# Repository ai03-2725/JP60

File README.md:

# JP60  
GH60互換疑似JISキーボードPCB  
GH60-compatible JIS-like hotswap keyboard PCB

Features  
- MITライセンスのもとでソース公開 / Open-source under the MIT license  
- Kailh製ソケットで全キーホットスワップ可能、はんだ付け無しで組み立て可能 / Fully hotswap  
- GH60対応の60％ケースで使用可能 / Compatible with GH60 standard cases  
- 一般的なキーサイズのみの日本語入力配列なので、GMKやePBTなどの標準キーキャップセットを使用可能 / Features a JIS-like key layout using standard keycap sizes   

[配列データ / Layout data](http://www.keyboard-layout-editor.com/#/gists/8acf5e6dbc672aa6a96d8ddba1245e7f)

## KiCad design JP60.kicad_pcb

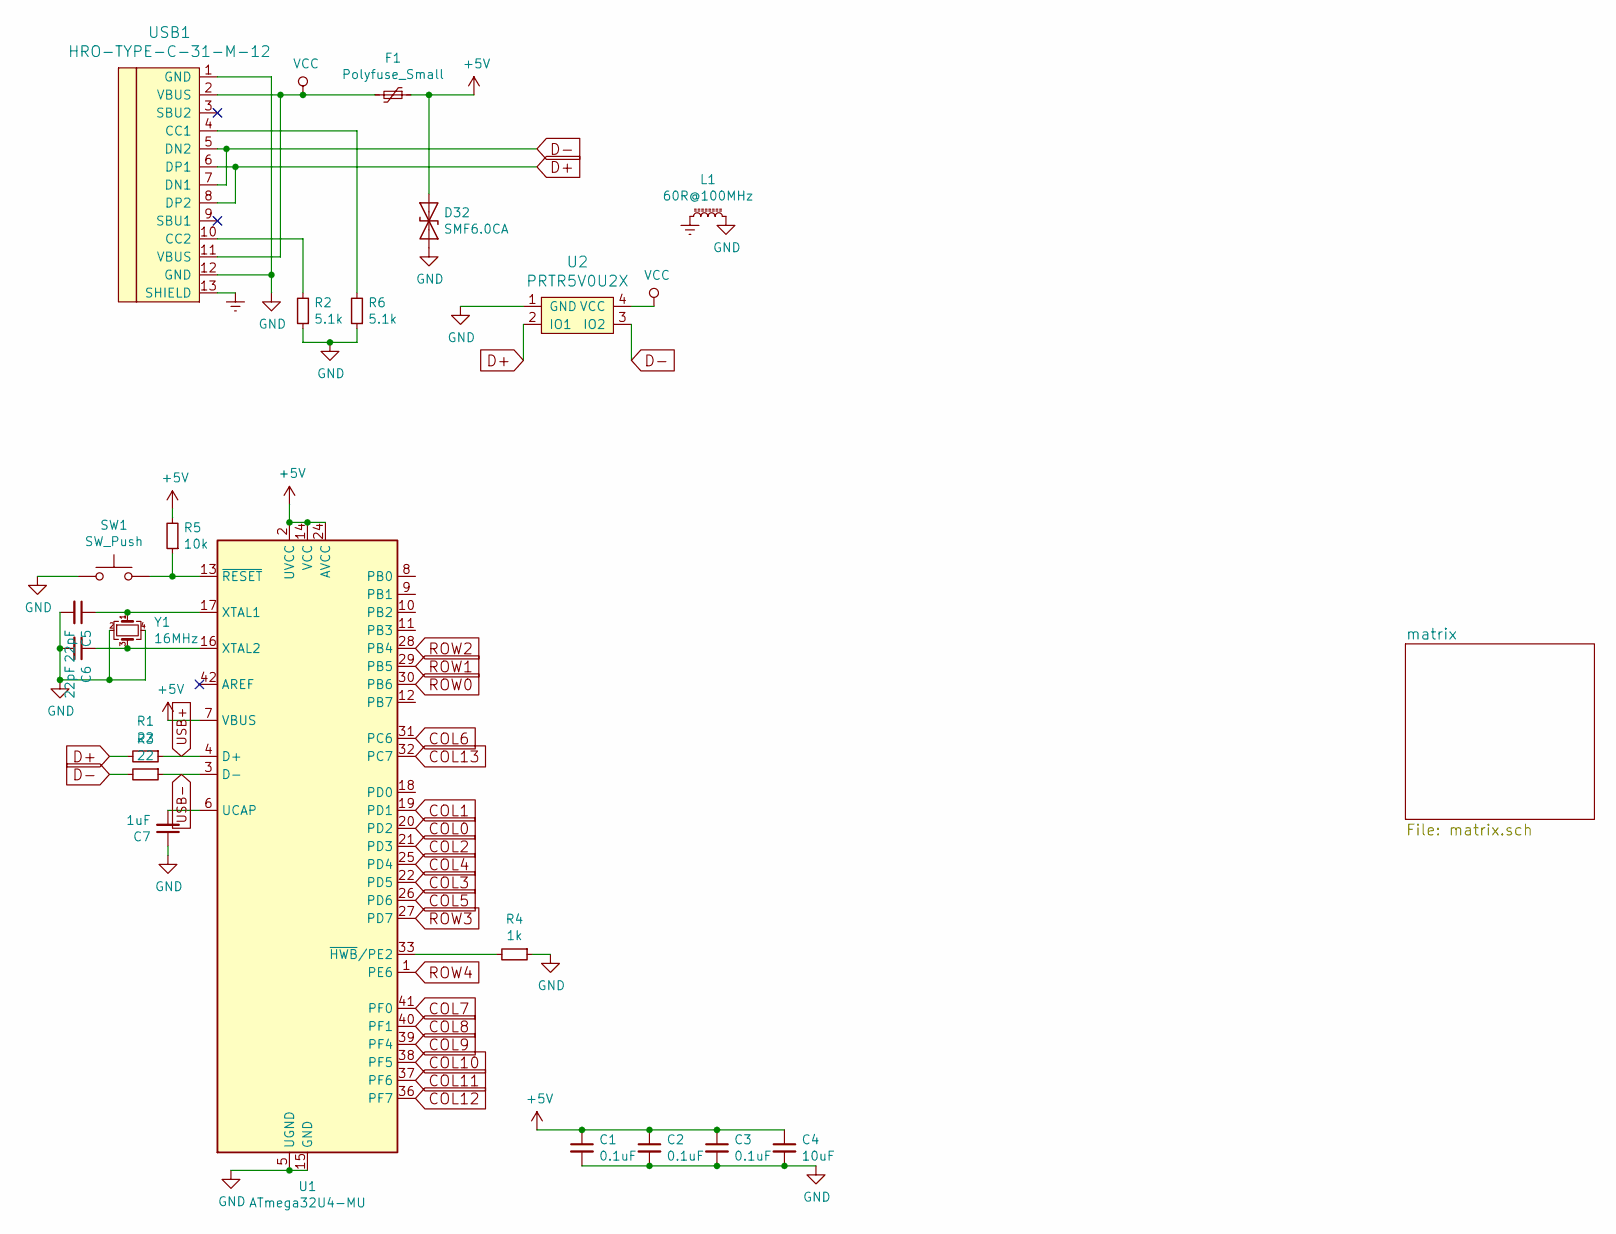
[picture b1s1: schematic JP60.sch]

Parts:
C1, C2, C3: 0.1uF; C_0603_1608Metric
C4: 10uF; C_0603_1608Metric
C5, C6: 22pF; C_0603_1608Metric
C7: 1uF; C_0603_1608Metric
D32: SMF6.0CA; D_SOD-123
F1: Polyfuse_Small; Fuse_1206_3216Metric
L1: 60R@100MHz; L_1206_3216Metric
R1, R3: 22; R_0603_1608Metric
R2, R6: 5.1k; R_0603_1608Metric
R4: 1k; R_0603_1608Metric
R5: 10k; R_0603_1608Metric
SW1: SW_Push; SW_SPST_TL3342
U1: ATmega32U4-MU; QFN-44-1EP_7x7mm_P0.5mm_EP5.2x5.2mm
U2: PRTR5V0U2X; SOT143B
USB1: HRO-TYPE-C-31-M-12; HRO-TYPE-C-31-M-12-Assembly
Y1: 16MHz; Crystal_SMD_3225-4Pin_3.2x2.5mm

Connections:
+5V: C1.1, C2.1, C3.1, C4.1, D32.2 (A2), F1.1, R5.2, U1.2 (UVCC), U1.7 (VBUS), U1.14 (VCC), U1.24 (AVCC), U1.34 (VCC), U1.44 (AVCC)
COL0: U1.20 (PD2); also elsewhere on the board
COL1: U1.19 (PD1); also elsewhere on the board
COL2: U1.21 (PD3); also elsewhere on the board
COL3: U1.22 (PD5); also elsewhere on the board
COL4: U1.25 (PD4); also elsewhere on the board
COL5: U1.26 (PD6); also elsewhere on the board
COL6: U1.31 (PC6); also elsewhere on the board
COL7: U1.41 (PF0); also elsewhere on the board
COL8: U1.40 (PF1); also elsewhere on the board
COL9: U1.39 (PF4); also elsewhere on the board
COL10: U1.38 (PF5); also elsewhere on the board
COL11: U1.37 (PF6); also elsewhere on the board
COL12: U1.36 (PF7); also elsewhere on the board
COL13: U1.32 (PC7); also elsewhere on the board
D+: R1.2, U2.2 (IO1), USB1.6 (DP1), USB1.8 (DP2)
D-: R3.2, U2.3 (IO2), USB1.5 (DN2), USB1.7 (DN1)
Earth: L1.1, USB1.13 (SHIELD)
GND: C1.2, C2.2, C3.2, C4.2, C5.2, C6.2, C7.1, D32.1 (A1), L1.2, R2.1, R4.1, R6.1, SW1.1, U1.5 (UGND), U1.15 (GND), U1.23 (GND), U1.35 (GND), U1.43 (GND), U1.45 (GND), U2.1 (GND), USB1.1 (GND), USB1.12 (GND), Y1.2, Y1.4
unnamed: C5.1, U1.17 (XTAL1), Y1.1
unnamed: C6.1, U1.16 (XTAL2), Y1.3
unnamed: C7.2, U1.6 (UCAP)
unnamed: R2.2, USB1.10 (CC2)
unnamed: R4.2, U1.33 (~HWB~/PE2)
unnamed: R5.1, SW1.2, U1.13 (~RESET)
unnamed: R6.2, USB1.4 (CC1)
ROW0: U1.30 (PB6); also elsewhere on the board
ROW1: U1.29 (PB5); also elsewhere on the board
ROW2: U1.28 (PB4); also elsewhere on the board
ROW3: U1.27 (PD7); also elsewhere on the board
ROW4: U1.1 (PE6); also elsewhere on the board
USB+: R1.1, U1.4 (D+)
USB-: R3.1, U1.3 (D-)
VCC: F1.2, U2.4 (VCC), USB1.2 (VBUS), USB1.11 (VBUS)

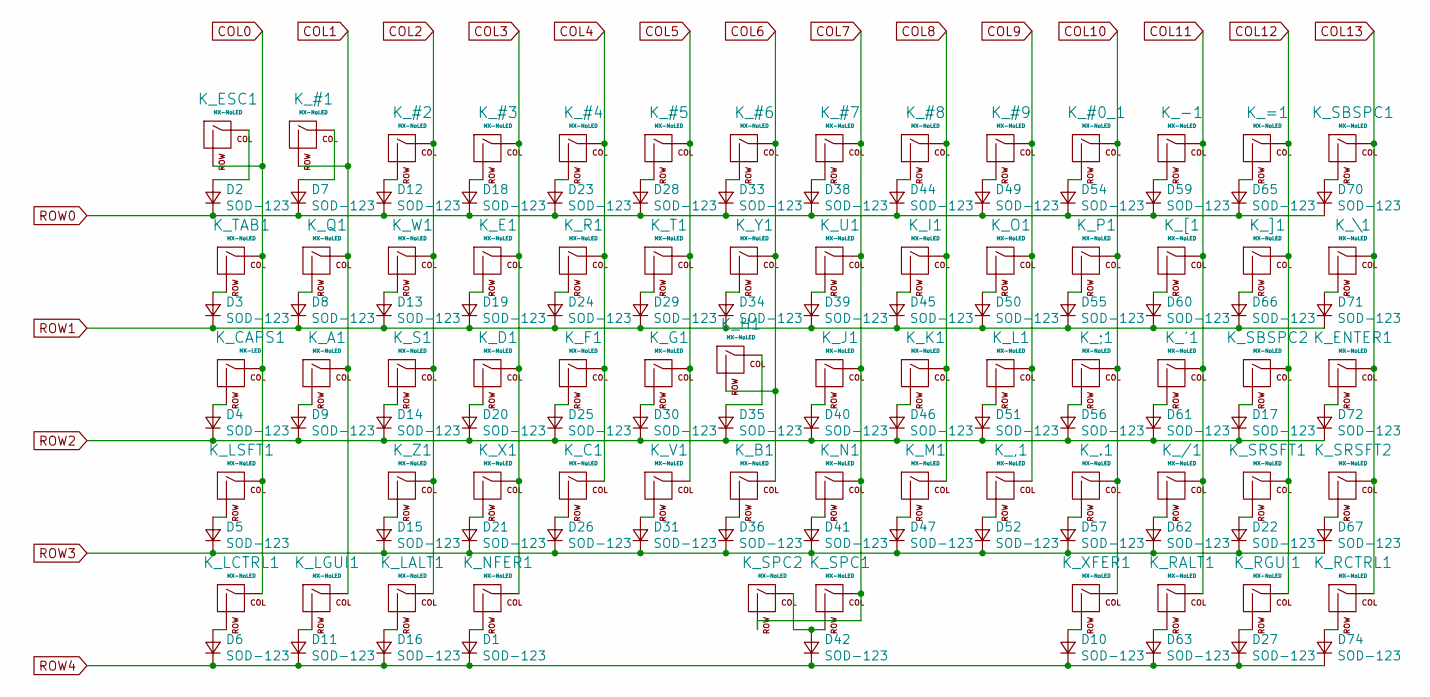
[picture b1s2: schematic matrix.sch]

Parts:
D1, D2, D3, D4, D5, D6, D7, D8, D9, D10, D11, D12, D13, D14, D15, D16, D17, D18, D19, D20, D21, D22, D23, D24, D25, D26, D27, D28, D29, D30, D31, D33, D34, D35, D36, D38, D39, D40, D41, D42, D44, D45, D46, D47, D49, D50, D51, D52, D54, D55, D56, D57, D59, D60, D61, D62, D63, D65, D66, D67, D70, D71, D72, D74: SOD-123; D_SOD-123
K_#0_1, K_#1, K_#2, K_#3, K_#4, K_#5, K_#6, K_#7, K_#8, K_#9: MX-NoLED; MXOnly-1U-Hotswap
K_'1: MX-NoLED; MXOnly-1U-Hotswap
K_,1: MX-NoLED; MXOnly-1U-Hotswap
K_-1: MX-NoLED; MXOnly-1U-Hotswap
K_.1: MX-NoLED; MXOnly-1U-Hotswap
K_/1: MX-NoLED; MXOnly-1U-Hotswap
K_;1: MX-NoLED; MXOnly-1U-Hotswap
K_=1: MX-NoLED; MXOnly-1U-Hotswap
K_A1: MX-NoLED; MXOnly-1U-Hotswap
K_B1: MX-NoLED; MXOnly-1U-Hotswap
K_C1: MX-NoLED; MXOnly-1U-Hotswap
K_CAPS1: MX-LED; MXOnly-1.75U-Hotswap
K_D1: MX-NoLED; MXOnly-1U-Hotswap
K_E1: MX-NoLED; MXOnly-1U-Hotswap
K_ENTER1: MX-NoLED; MXOnly-ISO-ROTATED-Hotswap
K_ESC1: MX-NoLED; MXOnly-1U-Hotswap
K_F1: MX-NoLED; MXOnly-1U-Hotswap
K_G1: MX-NoLED; MXOnly-1U-Hotswap
K_H1: MX-NoLED; MXOnly-1U-Hotswap
K_I1: MX-NoLED; MXOnly-1U-Hotswap
K_J1: MX-NoLED; MXOnly-1U-Hotswap
K_K1: MX-NoLED; MXOnly-1U-Hotswap
K_L1: MX-NoLED; MXOnly-1U-Hotswap
K_LALT1: MX-NoLED; MXOnly-1U-Hotswap
K_LCTRL1: MX-NoLED; MXOnly-1.25U-Hotswap
K_LGUI1: MX-NoLED; MXOnly-1U-Hotswap
K_LSFT1: MX-NoLED; MXOnly-2.25U-Hotswap
K_M1: MX-NoLED; MXOnly-1U-Hotswap
K_N1: MX-NoLED; MXOnly-1U-Hotswap
K_NFER1: MX-NoLED; MXOnly-1.25U-Hotswap
K_O1: MX-NoLED; MXOnly-1U-Hotswap
K_P1: MX-NoLED; MXOnly-1U-Hotswap
K_Q1: MX-NoLED; MXOnly-1U-Hotswap
K_R1: MX-NoLED; MXOnly-1U-Hotswap
K_RALT1: MX-NoLED; MXOnly-1U-Hotswap
K_RCTRL1: MX-NoLED; MXOnly-1.25U-Hotswap
K_RGUI1: MX-NoLED; MXOnly-1U-Hotswap
K_S1: MX-NoLED; MXOnly-1U-Hotswap
K_SBSPC1, K_SBSPC2: MX-NoLED; MXOnly-1U-Hotswap
K_SPC1: MX-NoLED; MXOnly-6U-Centered-Hotswap-ReversedStabilizers
K_SPC2: MX-NoLED; MXOnly-1U-Hotswap
K_SRSFT1: MX-NoLED; MXOnly-1U-Hotswap
K_SRSFT2: MX-NoLED; MXOnly-1.75U-Hotswap
K_T1: MX-NoLED; MXOnly-1U-Hotswap
K_TAB1: MX-NoLED; MXOnly-1.5U-Hotswap
K_U1: MX-NoLED; MXOnly-1U-Hotswap
K_V1: MX-NoLED; MXOnly-1U-Hotswap
K_W1: MX-NoLED; MXOnly-1U-Hotswap
K_X1: MX-NoLED; MXOnly-1U-Hotswap
K_XFER1: MX-NoLED; MXOnly-1.25U-Hotswap
K_Y1: MX-NoLED; MXOnly-1U-Hotswap
K_Z1: MX-NoLED; MXOnly-1U-Hotswap
K_[1: MX-NoLED; MXOnly-1U-Hotswap
K_\1: MX-NoLED; MXOnly-1U-Hotswap
K_]1: MX-NoLED; MXOnly-1U-Hotswap

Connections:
COL0: K_CAPS1.1 (COL), K_ESC1.2 (ROW), K_LCTRL1.1 (COL), K_LSFT1.1 (COL), K_TAB1.1 (COL); also elsewhere on the board
COL1: K_#1.2 (ROW), K_A1.1 (COL), K_LGUI1.1 (COL), K_Q1.1 (COL); also elsewhere on the board
COL2: K_#2.1 (COL), K_LALT1.1 (COL), K_S1.1 (COL), K_W1.1 (COL), K_Z1.1 (COL); also elsewhere on the board
COL3: K_#3.1 (COL), K_D1.1 (COL), K_E1.1 (COL), K_NFER1.1 (COL), K_X1.1 (COL); also elsewhere on the board
COL4: K_#4.1 (COL), K_C1.1 (COL), K_F1.1 (COL), K_R1.1 (COL); also elsewhere on the board
COL5: K_#5.1 (COL), K_G1.1 (COL), K_T1.1 (COL), K_V1.1 (COL); also elsewhere on the board
COL6: K_#6.1 (COL), K_B1.1 (COL), K_H1.2 (ROW), K_Y1.1 (COL); also elsewhere on the board
COL7: K_#7.1 (COL), K_J1.1 (COL), K_N1.1 (COL), K_SPC1.1 (COL), K_SPC2.2 (ROW), K_U1.1 (COL); also elsewhere on the board
COL8: K_#8.1 (COL), K_I1.1 (COL), K_K1.1 (COL), K_M1.1 (COL); also elsewhere on the board
COL9: K_#9.1 (COL), K_,1.1 (COL), K_L1.1 (COL), K_O1.1 (COL); also elsewhere on the board
COL10: K_#0_1.1 (COL), K_.1.1 (COL), K_;1.1 (COL), K_P1.1 (COL), K_XFER1.1 (COL); also elsewhere on the board
COL11: K_'1.1 (COL), K_-1.1 (COL), K_/1.1 (COL), K_RALT1.1 (COL), K_[1.1 (COL); also elsewhere on the board
COL12: K_=1.1 (COL), K_RGUI1.1 (COL), K_SBSPC2.1 (COL), K_SRSFT1.1 (COL), K_]1.1 (COL); also elsewhere on the board
COL13: K_ENTER1.1 (COL), K_RCTRL1.1 (COL), K_SBSPC1.1 (COL), K_SRSFT2.1 (COL), K_\1.1 (COL); also elsewhere on the board
unnamed: D1.2 (A), K_NFER1.2 (ROW)
unnamed: D2.2 (A), K_ESC1.1 (COL)
unnamed: D3.2 (A), K_TAB1.2 (ROW)
unnamed: D4.2 (A), K_CAPS1.2 (ROW)
unnamed: D5.2 (A), K_LSFT1.2 (ROW)
unnamed: D6.2 (A), K_LCTRL1.2 (ROW)
unnamed: D7.2 (A), K_#1.1 (COL)
unnamed: D8.2 (A), K_Q1.2 (ROW)
unnamed: D9.2 (A), K_A1.2 (ROW)
unnamed: D10.2 (A), K_XFER1.2 (ROW)
unnamed: D11.2 (A), K_LGUI1.2 (ROW)
unnamed: D12.2 (A), K_#2.2 (ROW)
unnamed: D13.2 (A), K_W1.2 (ROW)
unnamed: D14.2 (A), K_S1.2 (ROW)
unnamed: D15.2 (A), K_Z1.2 (ROW)
unnamed: D16.2 (A), K_LALT1.2 (ROW)
unnamed: D17.2 (A), K_SBSPC2.2 (ROW)
unnamed: D18.2 (A), K_#3.2 (ROW)
unnamed: D19.2 (A), K_E1.2 (ROW)
unnamed: D20.2 (A), K_D1.2 (ROW)
unnamed: D21.2 (A), K_X1.2 (ROW)
unnamed: D22.2 (A), K_SRSFT1.2 (ROW)
unnamed: D23.2 (A), K_#4.2 (ROW)
unnamed: D24.2 (A), K_R1.2 (ROW)
unnamed: D25.2 (A), K_F1.2 (ROW)
unnamed: D26.2 (A), K_C1.2 (ROW)
unnamed: D27.2 (A), K_RGUI1.2 (ROW)
unnamed: D28.2 (A), K_#5.2 (ROW)
unnamed: D29.2 (A), K_T1.2 (ROW)
unnamed: D30.2 (A), K_G1.2 (ROW)
unnamed: D31.2 (A), K_V1.2 (ROW)
unnamed: D33.2 (A), K_#6.2 (ROW)
unnamed: D34.2 (A), K_Y1.2 (ROW)
unnamed: D35.2 (A), K_H1.1 (COL)
unnamed: D36.2 (A), K_B1.2 (ROW)
unnamed: D38.2 (A), K_#7.2 (ROW)
unnamed: D39.2 (A), K_U1.2 (ROW)
unnamed: D40.2 (A), K_J1.2 (ROW)
unnamed: D41.2 (A), K_N1.2 (ROW)
unnamed: D42.2 (A), K_SPC1.2 (ROW), K_SPC2.1 (COL)
unnamed: D44.2 (A), K_#8.2 (ROW)
unnamed: D45.2 (A), K_I1.2 (ROW)
unnamed: D46.2 (A), K_K1.2 (ROW)
unnamed: D47.2 (A), K_M1.2 (ROW)
unnamed: D49.2 (A), K_#9.2 (ROW)
unnamed: D50.2 (A), K_O1.2 (ROW)
unnamed: D51.2 (A), K_L1.2 (ROW)
unnamed: D52.2 (A), K_,1.2 (ROW)
unnamed: D54.2 (A), K_#0_1.2 (ROW)
unnamed: D55.2 (A), K_P1.2 (ROW)
unnamed: D56.2 (A), K_;1.2 (ROW)
unnamed: D57.2 (A), K_.1.2 (ROW)
unnamed: D59.2 (A), K_-1.2 (ROW)
unnamed: D60.2 (A), K_[1.2 (ROW)
unnamed: D61.2 (A), K_'1.2 (ROW)
unnamed: D62.2 (A), K_/1.2 (ROW)
unnamed: D63.2 (A), K_RALT1.2 (ROW)
unnamed: D65.2 (A), K_=1.2 (ROW)
unnamed: D66.2 (A), K_]1.2 (ROW)
unnamed: D67.2 (A), K_SRSFT2.2 (ROW)
unnamed: D70.2 (A), K_SBSPC1.2 (ROW)
unnamed: D71.2 (A), K_\1.2 (ROW)
unnamed: D72.2 (A), K_ENTER1.2 (ROW)
unnamed: D74.2 (A), K_RCTRL1.2 (ROW)
ROW0: D2.1 (K), D7.1 (K), D12.1 (K), D18.1 (K), D23.1 (K), D28.1 (K), D33.1 (K), D38.1 (K), D44.1 (K), D49.1 (K), D54.1 (K), D59.1 (K), D65.1 (K), D70.1 (K); also elsewhere on the board
ROW1: D3.1 (K), D8.1 (K), D13.1 (K), D19.1 (K), D24.1 (K), D29.1 (K), D34.1 (K), D39.1 (K), D45.1 (K), D50.1 (K), D55.1 (K), D60.1 (K), D66.1 (K), D71.1 (K); also elsewhere on the board
ROW2: D4.1 (K), D9.1 (K), D14.1 (K), D17.1 (K), D20.1 (K), D25.1 (K), D30.1 (K), D35.1 (K), D40.1 (K), D46.1 (K), D51.1 (K), D56.1 (K), D61.1 (K), D72.1 (K); also elsewhere on the board
ROW3: D5.1 (K), D15.1 (K), D21.1 (K), D22.1 (K), D26.1 (K), D31.1 (K), D36.1 (K), D41.1 (K), D47.1 (K), D52.1 (K), D57.1 (K), D62.1 (K), D67.1 (K); also elsewhere on the board
ROW4: D1.1 (K), D6.1 (K), D10.1 (K), D11.1 (K), D16.1 (K), D27.1 (K), D42.1 (K), D63.1 (K), D74.1 (K); also elsewhere on the board

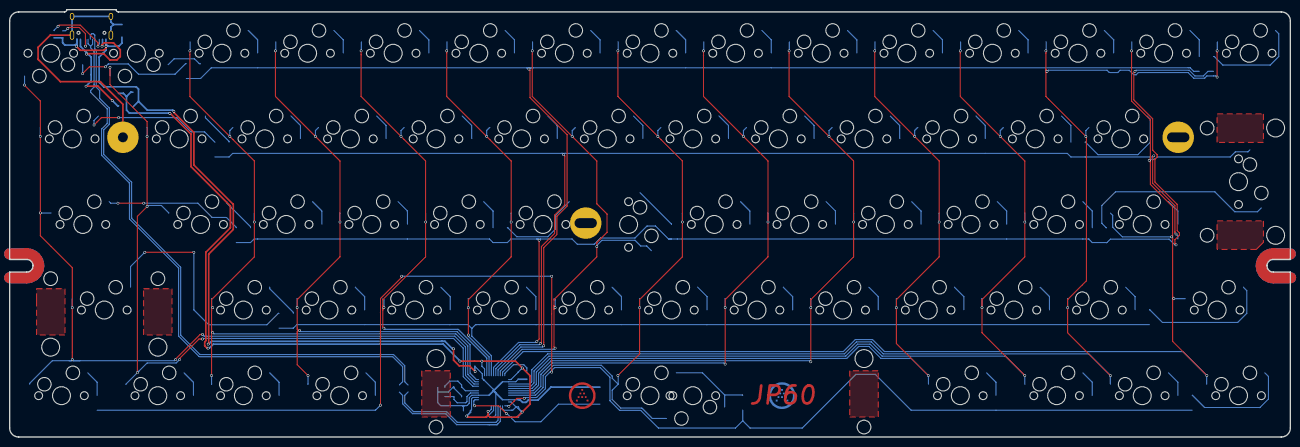
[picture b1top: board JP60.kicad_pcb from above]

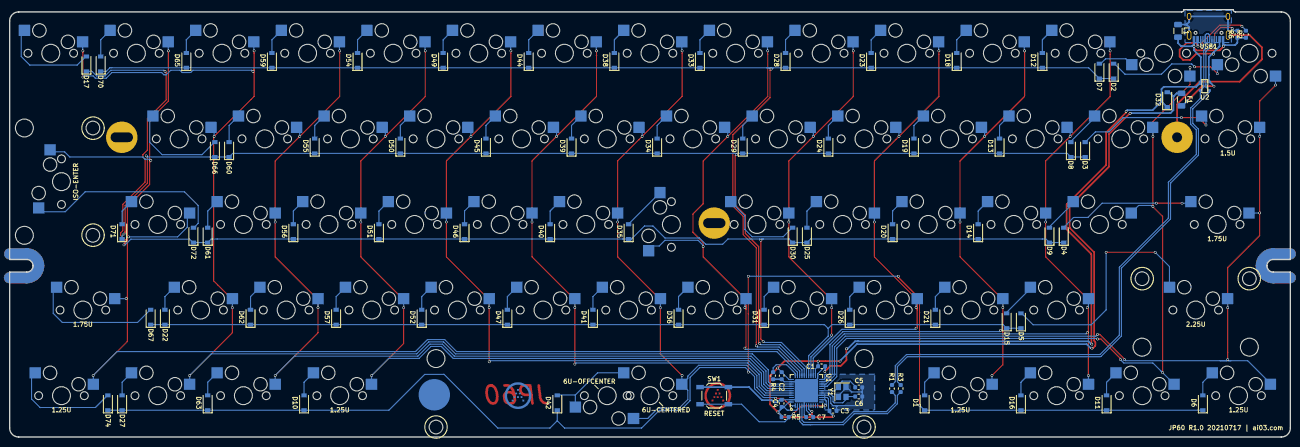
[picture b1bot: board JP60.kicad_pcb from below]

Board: 2 copper layers, 285.0 x 95.1 mm, 150 parts (85 on the bottom side), 98 nets.

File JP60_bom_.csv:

Component,Description,Part,References,Value,Footprint,Quantity Per PCB,Datasheet
1,"Unpolarized capacitor, small symbol",C_Small,C1 C2 C3,0.1uF,C_0603_1608Metric,3,~
2,"Unpolarized capacitor, small symbol",C_Small,C4,10uF,C_0603_1608Metric,1,~
3,"Unpolarized capacitor, small symbol",C_Small,C7,1uF,C_0603_1608Metric,1,~
4,"Unpolarized capacitor, small symbol",C_Small,C5 C6,22pF,C_0603_1608Metric,2,~
5,"Diode, small symbol",D_Small,D2 D3 D4 D5 D6 D7 D8 D9 D11 D12 D13 D14 D15 D16 D17 D18 D19 D20 D21 D22 D23 D24 D25 D26 D27 D28 D29 D30 D31 D33 D34 D35 D36 D38 D39 D40 D41 D42 D44 D45 D46 D47 D49 D50 D51 D52 D54 D55 D56 D57 D59 D60 D61 D62 D63 D65 D66 D67 D70 D71 D72 D74,SOD-123,D_SOD-123,62,~
6,"Generic connector, single row, 01x04, script generated (kicad-library-utils/schlib/autogen/connector/)",Conn_01x04,J1,Conn_01x04,JST-SR-4,1,~
7,,MX-NoLED,K_CAPS1,MX-LED,MXOnly-1.75U-Hotswap,1,
8,,MX-NoLED,"K_#0_1 K_#1 K_#2 K_#3 K_#4 K_#5 K_#6 K_#7 K_#8 K_#9 K_'1 K_,1 K_-1 K_.1 K_/1 K_;1 K_=1 K_A1 K_B1 K_C1 K_D1 K_E1 K_ESC1 K_F1 K_G1 K_H1 K_I1 K_J1 K_K1 K_L1 K_LGUI1 K_M1 K_N1 K_O1 K_P1 K_Q1 K_R1 K_RGUI1 K_S1 K_SBSPC1 K_SBSPC2 K_SRSFT2 K_T1 K_U1 K_V1 K_W1 K_X1 K_Y1 K_Z1 K_[1 K_]1",MX-NoLED,MXOnly-1U-Hotswap,51,
9,,MX-NoLED,K_ENTER1 K_LSFT1,MX-NoLED,MXOnly-2.25U-Hotswap,2,
10,,MX-NoLED,K_LALT1 K_LCTRL1 K_RALT1 K_RCTRL1 K_TAB1 K_\1,MX-NoLED,MXOnly-1.5U-Hotswap,6,
11,,MX-NoLED,K_SPC1,MX-NoLED,MXOnly-7U-Hotswap-ReversedStabilizers,1,
12,,MX-NoLED,K_SRSFT1,MX-NoLED,MXOnly-1.75U-Hotswap,1,
13,"Resistor, small symbol",R_Small,R5,10k,R_0603_1608Metric,1,~
14,"Resistor, small symbol",R_Small,R4,1k,R_0603_1608Metric,1,~
15,"Resistor, small symbol",R_Small,R1 R3,22,R_0603_1608Metric,2,~
16,"Push button switch, generic, two pins",SW_Push,SW1,SW_Push,SW_SPST_TL3342,1,~
17,"16MHz, 16kB Flash, 1.25kB SRAM, 512B EEPROM, USB 2.0, QFN-44",ATmega32U4-MU,U1,ATmega32U4-MU,QFN-44-1EP_7x7mm_P0.5mm_EP5.2x5.2mm,1,http://ww1.microchip.com/downloads/en/DeviceDoc/Atmel-7766-8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
18,"Four pin crystal, GND on pins 2 and 4, small symbol",Crystal_GND24_Small,Y1,16MHz,Crystal_SMD_3225-4Pin_3.2x2.5mm,1,~





Component Groups:,18
Component Count:,139
Fitted Components:,139
Number of PCBs:,1
Total components:,139
Schematic Version:,
Schematic Date:,
BoM Date:,12/3/2020 10:40:00 AM
Schematic Source:,C:\Users\ai03\Documents\GitHub\PolarisV2\PolarisV2.sch
KiCad Version:,Eeschema (5.1.4)-1

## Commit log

2021-07-17 Transition to git
2021-07-17 Update submod
2021-07-17 Finalize data
2021-07-17 Add renders
2021-07-17 Rename project files
2021-07-17 Add position and gerber files
2021-07-17 Make a basic readme
2021-07-17 Add license
2021-07-17 Add basic info to readme
2021-07-17 Add plate files
2021-07-17 Add rudimentary ja translation
2021-07-20 Update production files
2021-07-23 Fix mcu rotation in JLC prod file
2021-08-07 Fix plate data
2021-08-07 Update plate 3D model
2021-08-29 Add FR4 plate data
2023-04-18 Repair plate ISO enter stabilizer cutout
